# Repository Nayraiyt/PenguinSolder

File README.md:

# PenguinSolder
Simple PCB with a cute penguin drawing on it - For the Hack Club PCB Workshop :D

It is a 2 button parallel LED circuit, with a dapper little penguin guy.

Scematic: 

PCB:

3D:

Bill of Materials: 

2 Push Buttons

2 220 Ohm Resistors

2 LEDs

1 Battery Cell

Slack Username: @Naomi Cheng

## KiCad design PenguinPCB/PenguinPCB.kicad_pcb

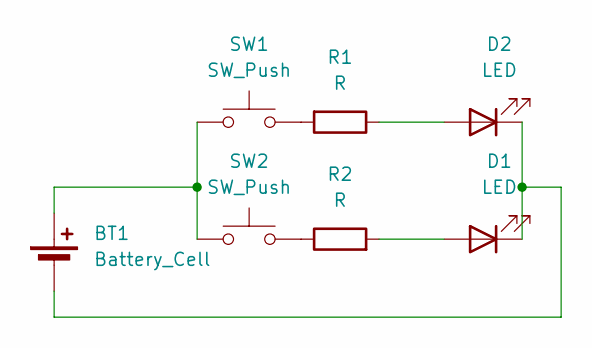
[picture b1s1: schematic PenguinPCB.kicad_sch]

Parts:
BT1: Battery_Cell; BatteryHolder_Keystone_3034_1x20mm
D1, D2: LED; LED_D5.0mm
R1, R2: R; R_Axial_DIN0207_L6.3mm_D2.5mm_P7.62mm_Horizontal
SW1, SW2: SW_Push; SW_PUSH_6mm

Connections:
unnamed: BT1.1 (+), SW1.1, SW2.1
unnamed: BT1.2 (-), D1.1 (K), D2.1 (K)
unnamed: D1.2 (A), R2.2
unnamed: D2.2 (A), R1.1
unnamed: R1.2, SW1.2
unnamed: R2.1, SW2.2

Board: 2 copper layers, 7 parts (0 on the bottom side), 6 nets, no tracks yet.
